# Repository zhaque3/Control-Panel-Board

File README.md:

# Control-Panel-Board
Control Panel Board for Timberwolf EV prototype

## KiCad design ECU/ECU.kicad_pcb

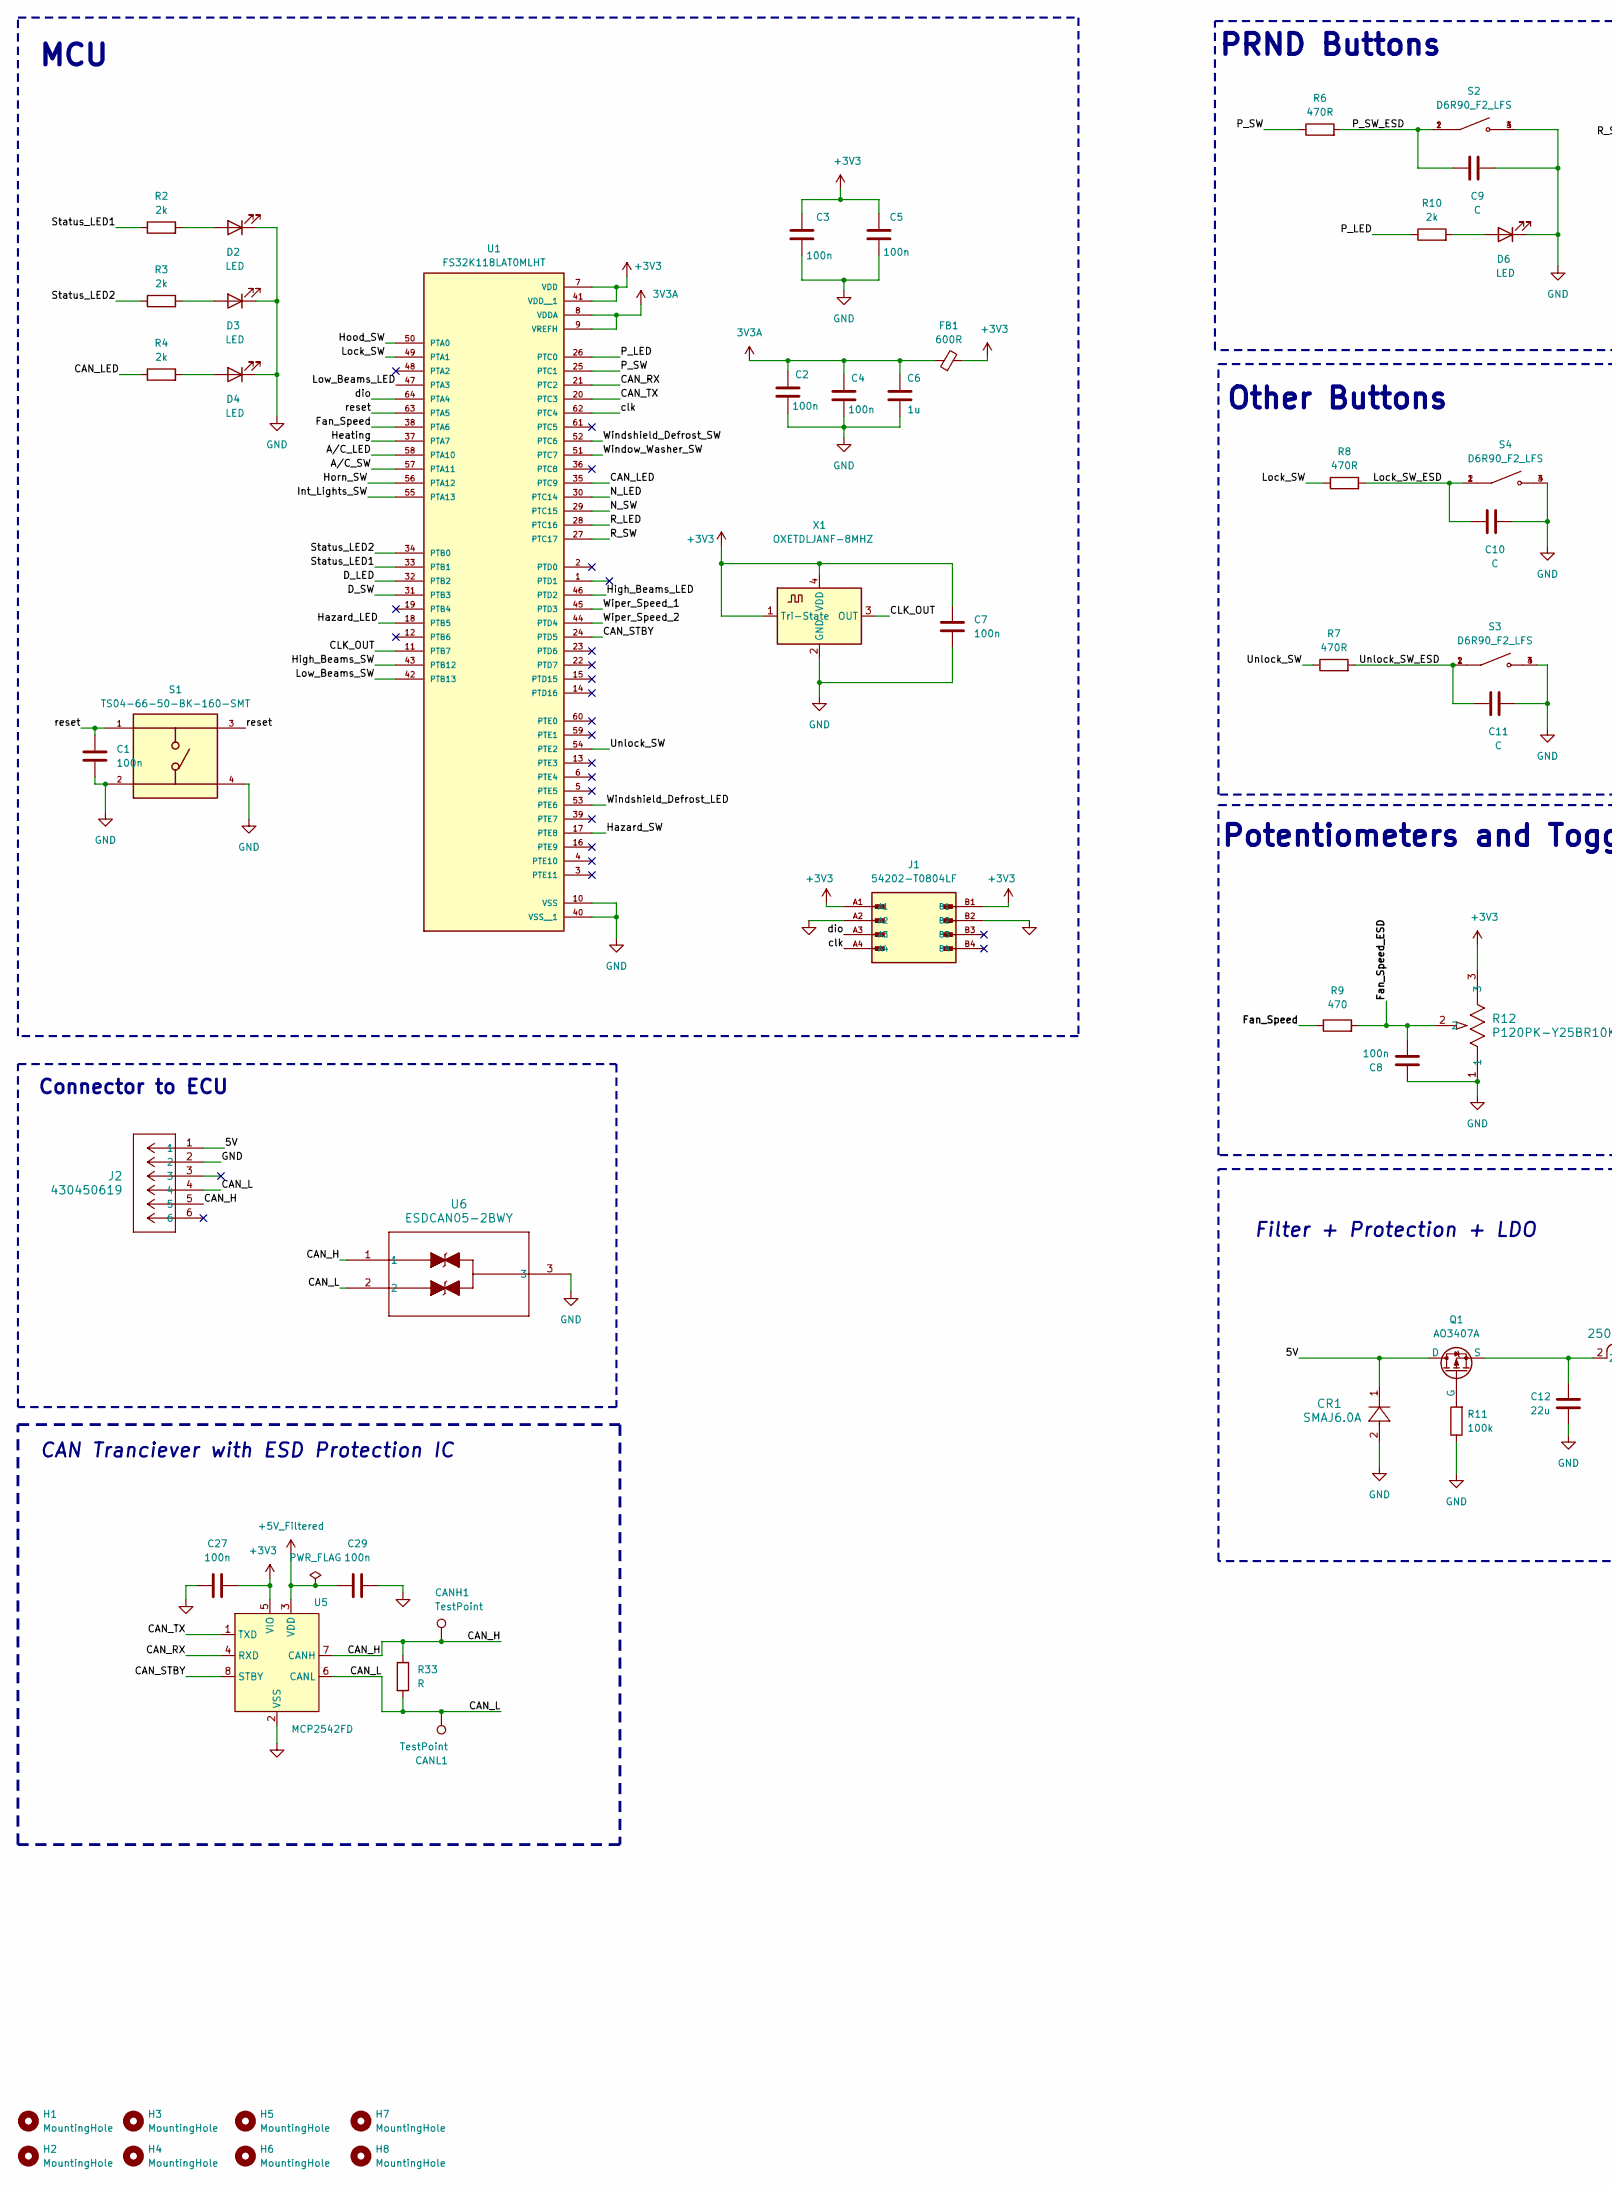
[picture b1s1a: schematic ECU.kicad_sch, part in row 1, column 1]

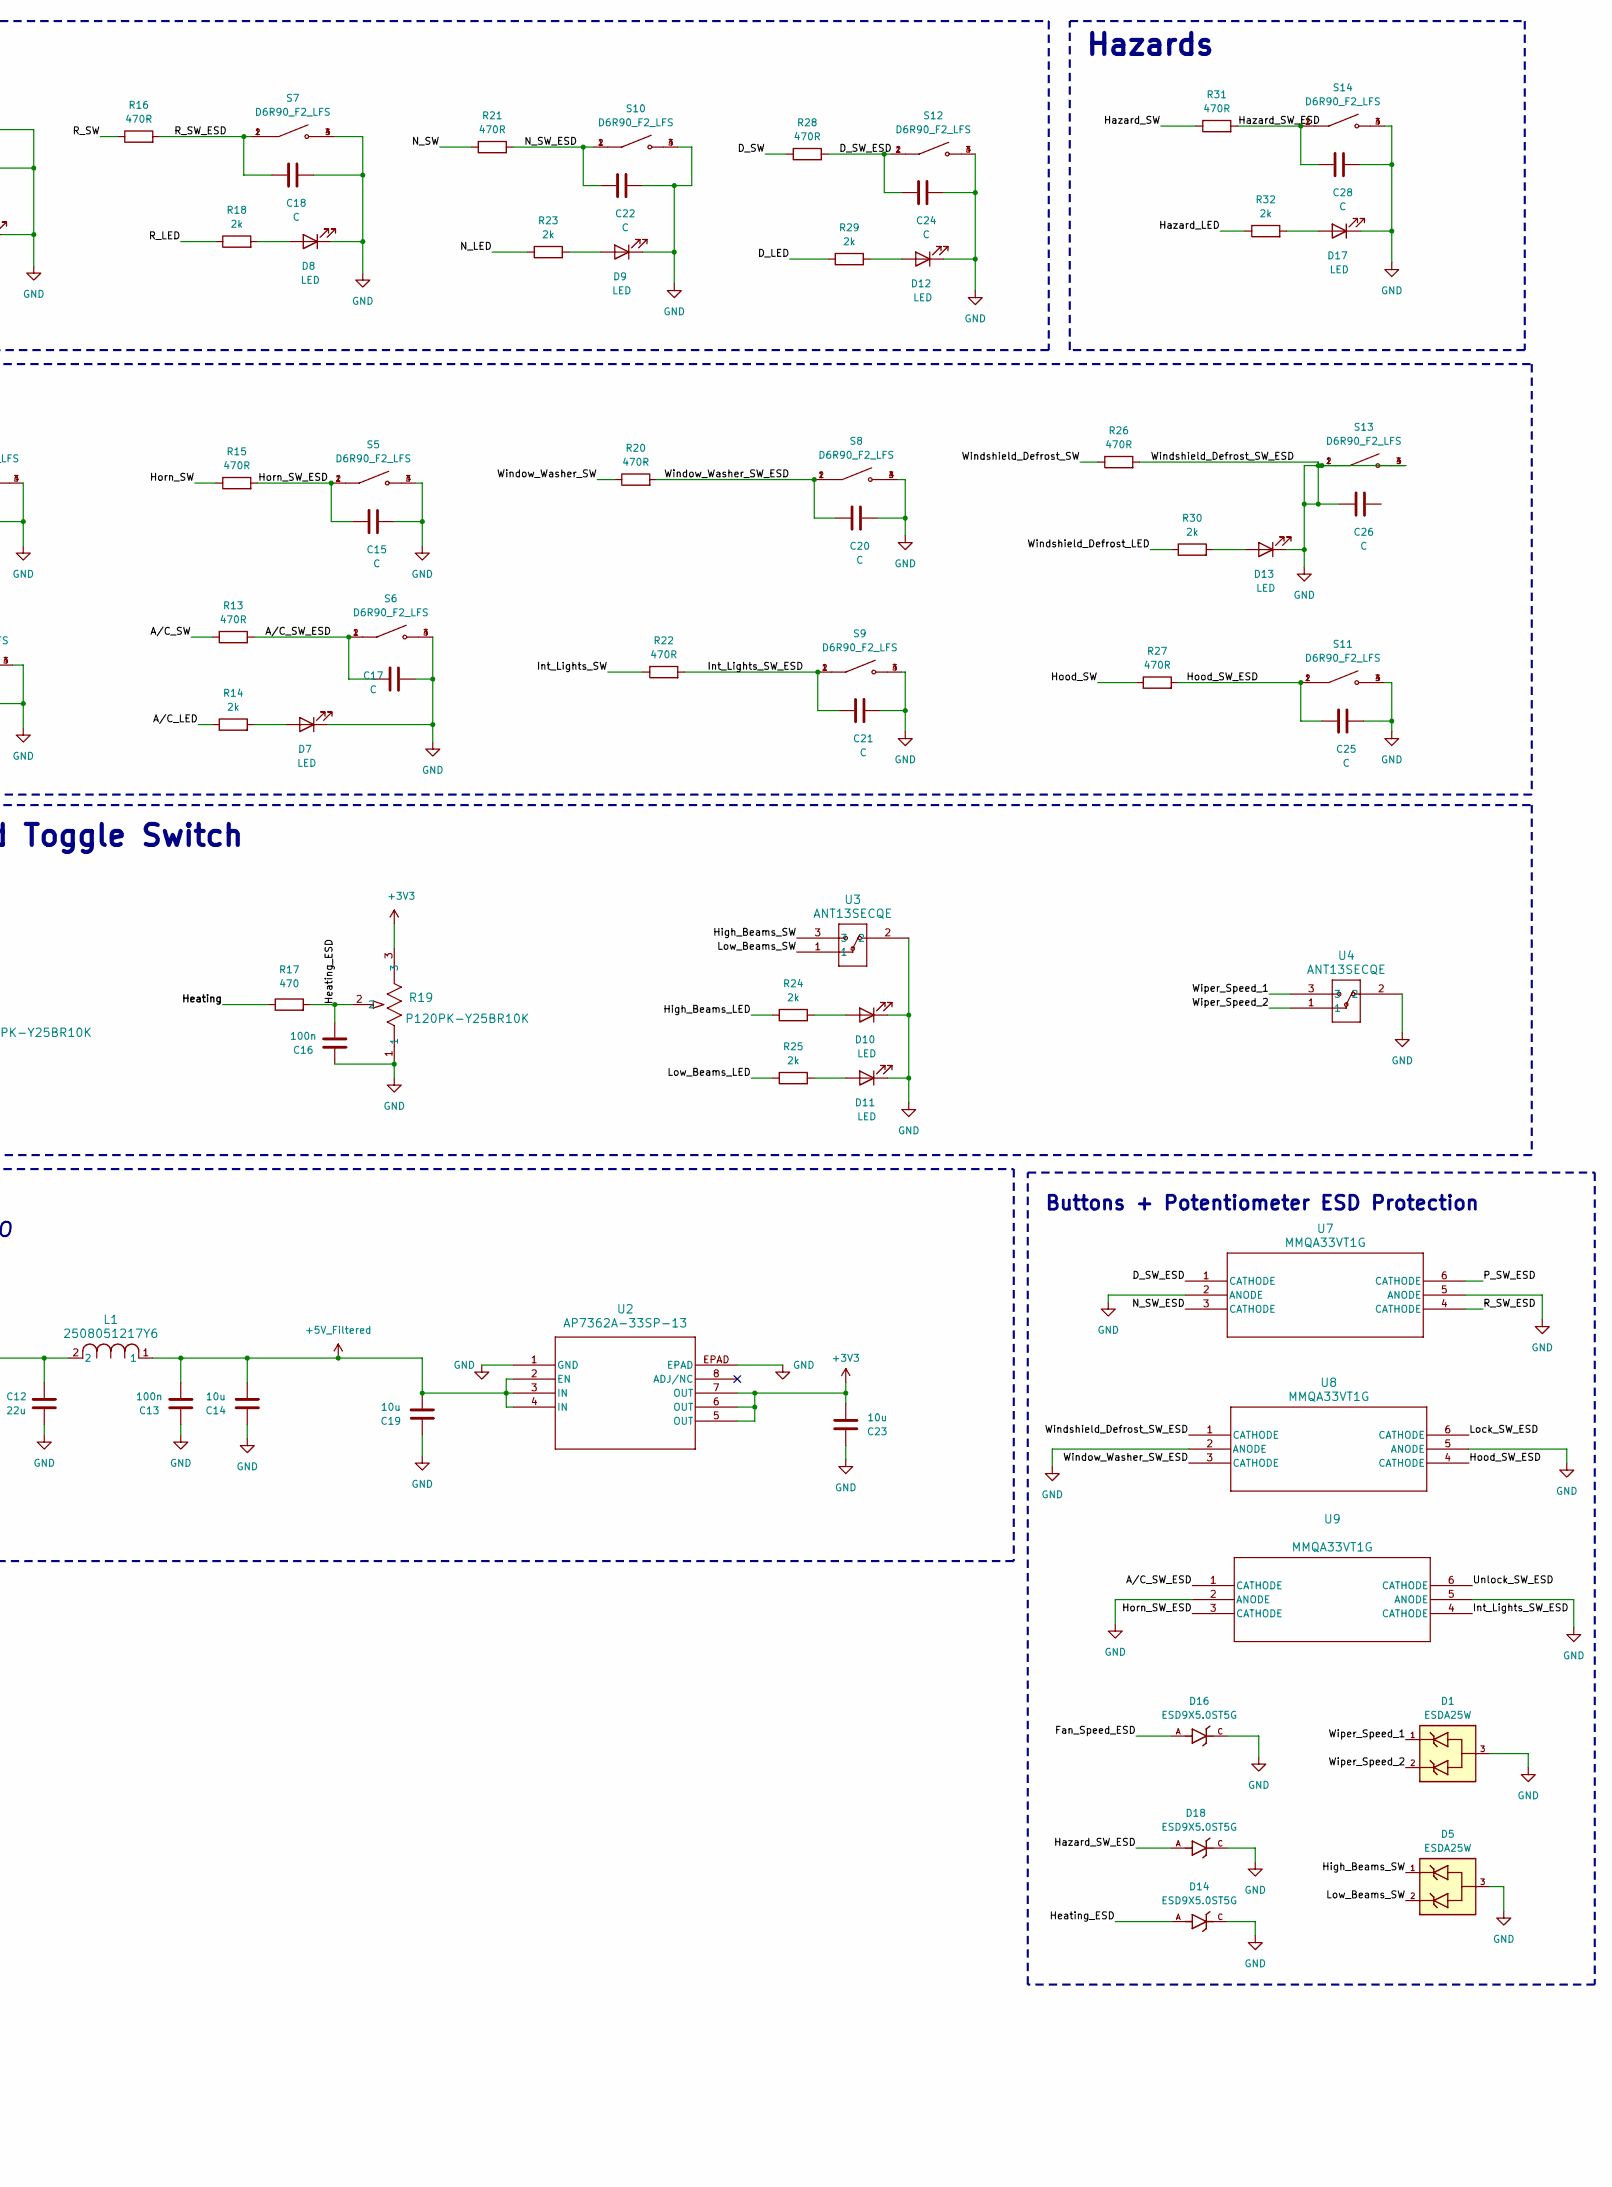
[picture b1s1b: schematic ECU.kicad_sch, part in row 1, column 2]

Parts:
C1, C2, C3, C4, C5: 100n; C_0805_2012Metric
C6: 1u; C_0805_2012Metric
C7: 100n; C_0603_1608Metric
C8, C13, C16, C27, C29: 100n; C_0805_2012Metric; JLCPCB Part#(Optional) C1525
C9, C10, C11, C15, C17, C18, C20, C21, C22, C24, C25, C26, C28: C; C_0805_2012Metric
C12: 22u; C_1210_3225Metric
C14, C19, C23: 10u; C_0805_2012Metric; JLCPCB Part#(Optional) C1525
CANH1: TestPoint; TestPoint_Pad_D1.5mm
CANL1: TestPoint; TestPoint_Pad_D1.5mm
CR1: SMAJ6.0A; SMASeries_LTF
D1, D5: ESDA25W; SOT65P210X110-3N; PARTREV 2
D2, D3, D4, D6, D7, D8, D9, D10, D11, D12, D13, D17: LED; LED_0805_2012Metric
D14, D16, D18: ESD9X5.0ST5G; SODFL1006X43N; PARTREV 8
FB1: 600R; L_0805_2012Metric
H1, H2, H3, H4, H5, H6, H7, H8: MountingHole; MountingHole_3.5mm
J1: 54202-T0804LF; AMPHENOL_54202-T0804LF; PARTREV AC
J2: 430450619; CONN_SD-43045-007_06_MOL
L1: 2508051217Y6; IND_25_0805_FRT
Q1: AO3407A; SOT-23-3L_AOS
R2, R3, R4, R10, R14, R18, R23, R24, R25, R29, R30, R32: 2k; R_0805_2012Metric
R6, R7, R8, R13, R15, R16, R20, R21, R22, R26, R27, R28, R31: 470R; R_0805_2012Metric
R9, R17: 470; R_0805_2012Metric
R11: 100k; R_0805_2012Metric
R12, R19: P120PK-Y25BR10K; POT_P120PK-x25_TTE
R33: R; R_0805_2012Metric
S1: TS04-66-50-BK-160-SMT; SW_TS04-66-50-BK-160-SMT; PARTREV 1.0
S2, S3, S4, S5, S6, S7, S8, S9, S10, S11, S12, S13, S14: D6R90_F2_LFS; SW_D6R90_F2_LFS; PARTREV 21 Feb 22
U1: FS32K118LAT0MLHT; QFP50P1200X1200X160-64N; PARTREV 14
U2: AP7362A-33SP-13; SO-8EP_3P9X4P9_DIO
U3, U4: ANT13SECQE; ANT13SEC_CRS; Digikey # 2449-ANT13SECQE-ND
U5: MCP2542FD; SOIC8_4P9X3P9MC_MCH
U6: ESDCAN05-2BWY; SOT323-3L_STM
U7, U8, U9: MMQA33VT1G; SC74-6_3P1X1P7_ONS
X1: OXETDLJANF-8MHZ; XTAL_ASE-8.000MHZ-LC-T

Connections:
3V3A: C2.1, C4.1, C6.1, FB1.1, U1.8 (VDDA), U1.9 (VREFH)
+3V3: C3.1, C5.1, C7.1, C23.1, C27.1, FB1.2, J1.A1, J1.B1, R12.3, R19.3, U1.7 (VDD), U1.41 (VDD__1), U2.5 (OUT), U2.6 (OUT), U2.7 (OUT), U5.5 (VIO), X1.1 (Tri-State), X1.4 (VDD)
+5V_Filtered: C13.1, C14.1, C19.1, C29.2, L1.1, U2.2 (EN), U2.3 (IN), U2.4 (IN), U5.3 (VDD)
/5V: CR1.1, J2.1, Q1.1 (D)
/A/C_LED: R14.1, U1.58 (PTA10)
/A/C_SW: R13.1, U1.57 (PTA11)
/A/C_SW_ESD: C17.2, R13.2, S6.1, S6.2, U9.1 (CATHODE)
/CAN_H: CANH1.1, J2.5, R33.1, U5.7 (CANH), U6.1
/CAN_L: CANL1.1, J2.4, R33.2, U5.6 (CANL), U6.2
/CAN_LED: R4.1, U1.35 (PTC9)
/CAN_RX: U1.21 (PTC2), U5.4 (RXD)
/CAN_STBY: U1.24 (PTD5), U5.8 (STBY)
/CAN_TX: U1.20 (PTC3), U5.1 (TXD)
/CLK_OUT: U1.11 (PTB7), X1.3 (OUT)
/D_LED: R29.1, U1.32 (PTB2)
/D_SW: R28.1, U1.31 (PTB3)
/D_SW_ESD: C24.2, R28.2, S12.1, S12.2, U7.1 (CATHODE)
/Fan_Speed: R9.1, U1.38 (PTA6)
/Fan_Speed_ESD: C8.1, D16.A, R9.2, R12.2
/Hazard_LED: R32.1, U1.18 (PTB5)
/Hazard_SW: R31.1, U1.17 (PTE8)
/Hazard_SW_ESD: C28.2, D18.A, R31.2, S14.1, S14.2
/Heating: R17.1, U1.37 (PTA7)
/Heating_ESD: C16.1, D14.A, R17.2, R19.2
/High_Beams_LED: R24.1, U1.46 (PTD2)
/High_Beams_SW: D5.1, U1.43 (PTB12), U3.3
/Hood_SW: R27.1, U1.50 (PTA0)
/Hood_SW_ESD: C25.2, R27.2, S11.1, S11.2, U8.4 (CATHODE)
/Horn_SW: R15.1, U1.56 (PTA12)
/Horn_SW_ESD: C15.2, R15.2, S5.1, S5.2, U9.3 (CATHODE)
/Int_Lights_SW: R22.1, U1.55 (PTA13)
/Int_Lights_SW_ESD: C21.2, R22.2, S9.1, S9.2, U9.4 (CATHODE)
/Lock_SW: R8.1, U1.49 (PTA1)
/Lock_SW_ESD: C10.2, R8.2, S4.1, S4.2, U8.6 (CATHODE)
/Low_Beams_LED: R25.1, U1.47 (PTA3)
/Low_Beams_SW: D5.2, U1.42 (PTB13), U3.1
/N_LED: R23.1, U1.30 (PTC14)
/N_SW: R21.1, U1.29 (PTC15)
/N_SW_ESD: C22.2, R21.2, S10.1, S10.2, U7.3 (CATHODE)
/P_LED: R10.1, U1.26 (PTC0)
/P_SW: R6.1, U1.25 (PTC1)
/P_SW_ESD: C9.2, R6.2, S2.1, S2.2, U7.6 (CATHODE)
/R_LED: R18.1, U1.28 (PTC16)
/R_SW: R16.1, U1.27 (PTC17)
/R_SW_ESD: C18.2, R16.2, S7.1, S7.2, U7.4 (CATHODE)
/Status_LED1: R2.1, U1.33 (PTB1)
/Status_LED2: R3.1, U1.34 (PTB0)
/Unlock_SW: R7.1, U1.54 (PTE2)
/Unlock_SW_ESD: C11.2, R7.2, S3.1, S3.2, U9.6 (CATHODE)
/Window_Washer_SW: R20.1, U1.51 (PTC7)
/Window_Washer_SW_ESD: C20.2, R20.2, S8.1, S8.2, U8.3 (CATHODE)
/Windshield_Defrost_LED: R30.1, U1.53 (PTE6)
/Windshield_Defrost_SW: R26.1, U1.52 (PTC6)
/Wiper_Speed_1: D1.1, U1.45 (PTD3), U4.3
/Wiper_Speed_2: D1.2, U1.44 (PTD4), U4.1
/clk: J1.A4, U1.62 (PTC4)
/dio: J1.A3, U1.64 (PTA4)
/reset: C1.1, S1.1, S1.3, U1.63 (PTA5)
unnamed: D2.2 (A), R2.2
unnamed: D3.2 (A), R3.2
unnamed: D4.2 (A), R4.2
unnamed: D6.2 (A), R10.2
unnamed: D7.2 (A), R14.2
unnamed: D8.2 (A), R18.2
unnamed: D9.2 (A), R23.2
unnamed: D10.2 (A), R24.2
unnamed: D11.2 (A), R25.2
unnamed: D12.2 (A), R29.2
unnamed: D13.2 (A), R30.2
unnamed: D17.2 (A), R32.2
unnamed: Q1.2 (G), R11.2
unnamed: C12.1, L1.2, Q1.3 (S)

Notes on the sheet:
Filter + Protection + LDO
Buttons + Potentiometer ESD Protection
PRND Buttons
Hazards
CAN Tranciever with ESD Protection IC
Potentiometers and Toggle Switch
MCU
Connector to ECU
Other Buttons

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
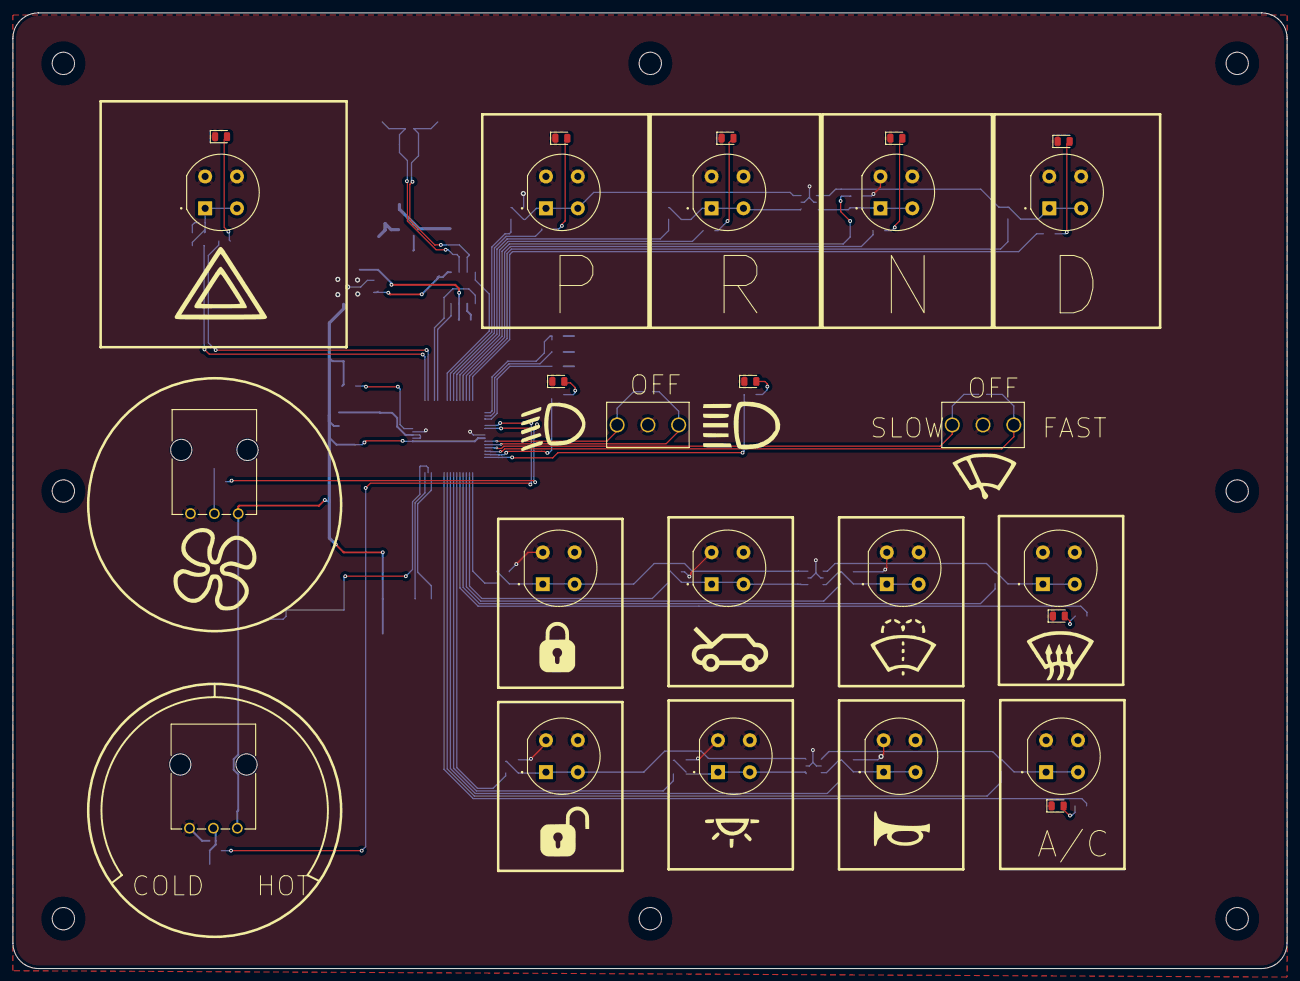
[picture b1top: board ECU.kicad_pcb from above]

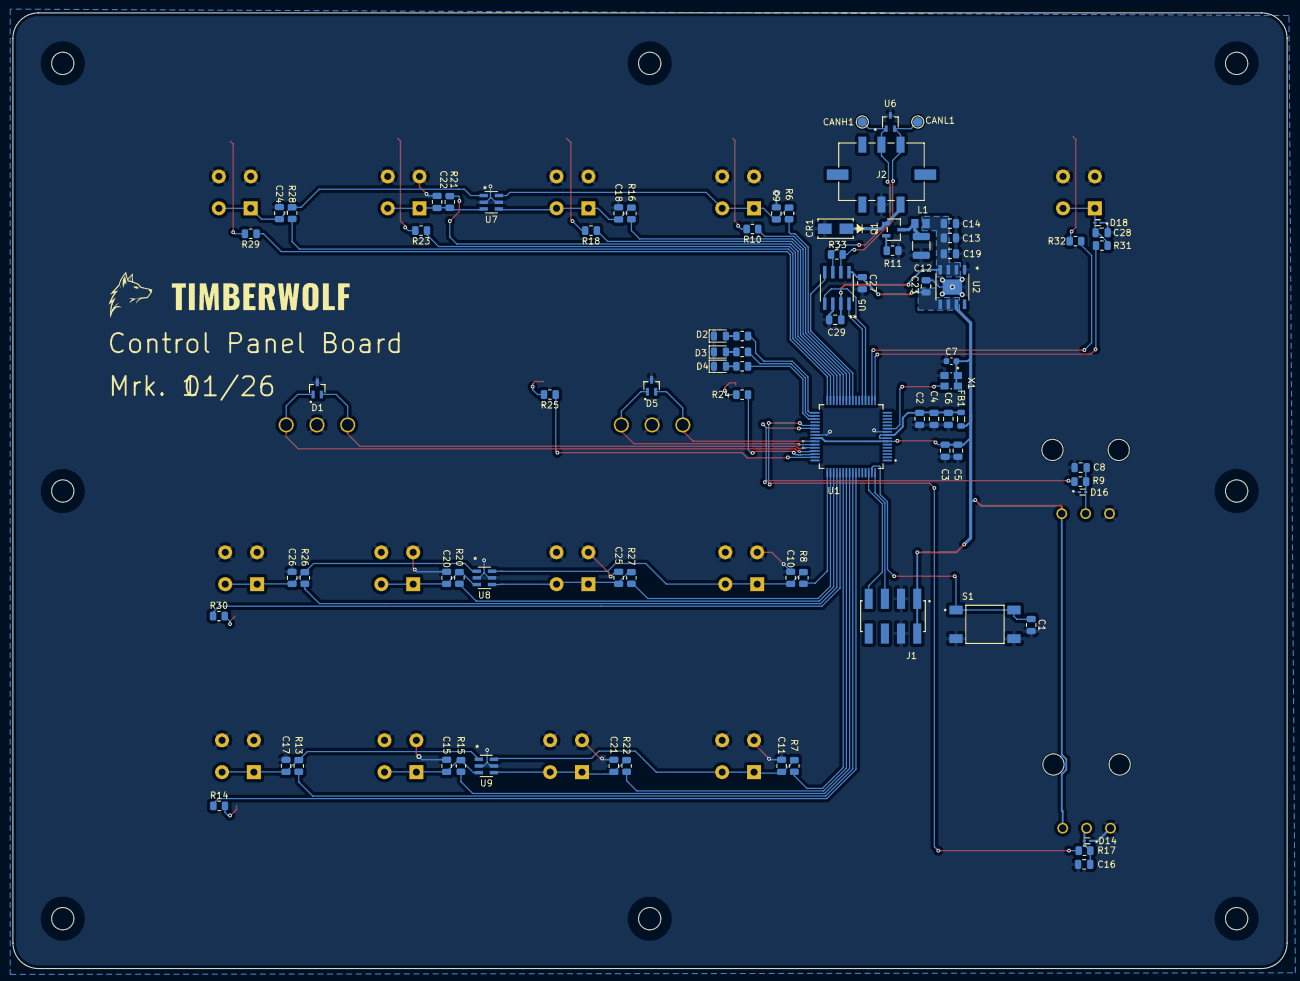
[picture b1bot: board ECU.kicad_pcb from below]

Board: 2 copper layers, 200.0 x 150.0 mm, 117 parts (83 on the bottom side), 74 nets.

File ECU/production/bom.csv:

Designator,Footprint,Quantity,Value,LCSC Part #
"C1, C13, C16, C2, C27, C29, C3, C4, C5, C8",0805,10,100n,
"C10, C11, C15, C17, C18, C20, C21, C22, C24, C25, C26, C28, C9",0805,13,C,
C12,1210,1,22u,
"C14, C19, C23",0805,3,10u,
C6,0805,1,1u,
C7,0603,1,100n,
"CANH1, CANL1",TestPoint_Pad_D1.5mm,2,TestPoint,
CR1,SMASeries_LTF,1,SMAJ6.0A,
"D1, D5",SOT65P210X110-3N,2,ESDA25W,
"D10, D11, D12, D13, D17, D2, D3, D4, D6, D7, D8, D9",0805,12,LED,
"D14, D16, D18",SODFL1006X43N,3,ESD9X5.0ST5G,
FB1,0805,1,600R,
J1,AMPHENOL_54202-T0804LF,1,54202-T0804LF,
J2,CONN_SD-43045-007_06_MOL,1,430450619,
L1,IND_25_0805_FRT,1,2508051217Y6,
Q1,SOT-23-3L_AOS,1,AO3407A,
"R10, R14, R18, R2, R23, R24, R25, R29, R3, R30, R32, R4",0805,12,2k,
R11,0805,1,100k,
"R12, R19",POT_P120PK-x25_TTE,2,P120PK-Y25BR10K,
"R13, R15, R16, R20, R21, R22, R26, R27, R28, R31, R6, R7, R8",0805,13,470R,
"R17, R9",0805,2,470,
R33,0805,1,R,
S1,SW_TS04-66-50-BK-160-SMT,1,TS04-66-50-BK-160-SMT,
"S10, S11, S12, S13, S14, S2, S3, S4, S5, S6, S7, S8, S9",SW_D6R90_F2_LFS,13,D6R90_F2_LFS,
U1,QFP50P1200X1200X160-64N,1,FS32K118LAT0MLHT,
U2,SO-8EP_3P9X4P9_DIO,1,AP7362A-33SP-13,
"U3, U4",ANT13SEC_CRS,2,ANT13SECQE,
U5,SOIC8_4P9X3P9MC_MCH,1,MCP2542FD,
U6,SOT323-3L_STM,1,ESDCAN05-2BWY,
"U7, U8, U9",SC74-6_3P1X1P7_ONS,3,MMQA33VT1G,
X1,XTAL_ASE-8.000MHZ-LC-T,1,OXETDLJANF-8MHZ,

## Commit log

2026-01-28 added PCB
